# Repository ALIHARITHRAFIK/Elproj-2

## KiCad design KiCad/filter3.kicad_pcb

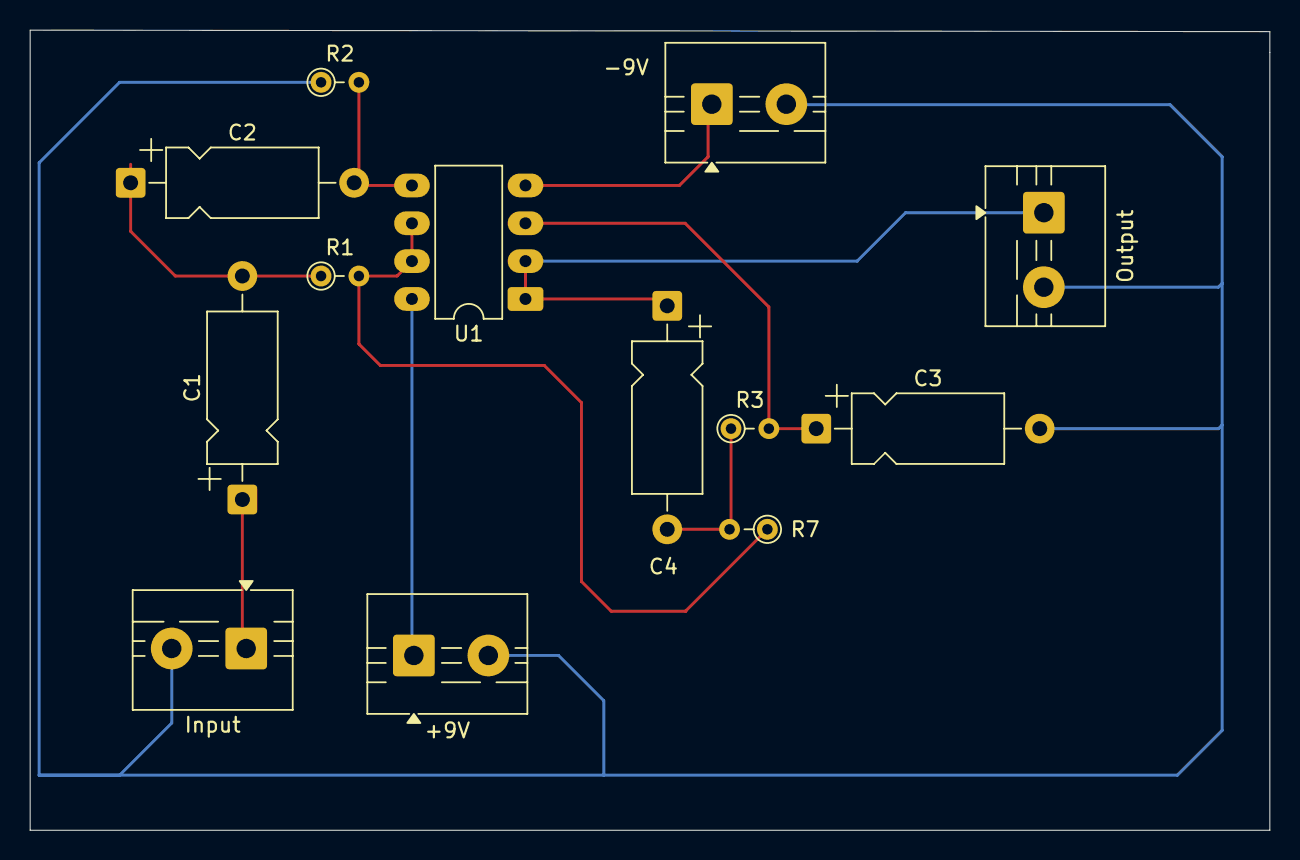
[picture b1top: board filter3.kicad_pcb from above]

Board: 2 copper layers, 83.2 x 53.7 mm, 13 parts (0 on the bottom side), 10 nets.

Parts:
+9V: Screw_Terminal_01x02; TerminalBlock_MaiXu_MX126-5.0-02P_1x02_P5.00mm
-9V: -9V; TerminalBlock_MaiXu_MX126-5.0-02P_1x02_P5.00mm
C1, C2: 100n; CP_Axial_L10.0mm_D4.5mm_P15.00mm_Horizontal
C3, C4: 10n; CP_Axial_L10.0mm_D4.5mm_P15.00mm_Horizontal
Input: Screw_Terminal_01x02; TerminalBlock_MaiXu_MX126-5.0-02P_1x02_P5.00mm
Output: Output; TerminalBlock_MaiXu_MX126-5.0-02P_1x02_P5.00mm
R1: 12k; R_Axial_DIN0204_L3.6mm_D1.6mm_P2.54mm_Vertical
R2: 3.9k; R_Axial_DIN0204_L3.6mm_D1.6mm_P2.54mm_Vertical
R3, R7: 3.3k; R_Axial_DIN0204_L3.6mm_D1.6mm_P2.54mm_Vertical
U1: NE5532; DIP-8_W7.62mm_LongPads

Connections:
+9V: +9V.1, U1.8 (V+)
-9V: -9V.1, U1.4 (V-)
GND: +9V.2, -9V.2, C3.2, Input.2, Output.2, R2.1
unnamed: C1.2, C2.1, R1.1
unnamed: C4.2, R3.1, R7.2
unnamed: C3.1, R3.2, U1.3 (+)
unnamed: C2.2, R2.2, U1.5 (+)
unnamed: R1.2, R7.1, U1.6 (-), U1.7
Signal: C4.1, Output.1, U1.1, U1.2 (-)
VAC: C1.1, Input.1

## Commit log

2025-12-03 Initial commit av KiCad-projekt
2026-02-13 Första uppladdningen av KiCad-projektet
2026-02-22 filtret
2026-02-22 nya filtret
2026-02-22 nytt filter3
2026-02-22 filter3
